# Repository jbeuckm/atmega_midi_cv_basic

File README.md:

# atmega_midi_cv_basic
Simple gate+pitch+velocity with one 4822

Portamento time is controlled by MIDI CC #5.

When more than one MIDI note is active, the frequency CV is set according to the value of MIDI CC #80 as follows:

CC #80 | Note Priority
--- | ---   
0-31 | Lowest Note
32-63 | Highest Note
64-127 | Highest Velocity (default)

The MIDI channel can be set by sending the following SYSEX message: 
`0x77 0x16 0x01 0x00 0xcc` where cc is the new channel.

Parts placement for Release v0.5:

For 6N137 instead of 6N138, build with these changes:

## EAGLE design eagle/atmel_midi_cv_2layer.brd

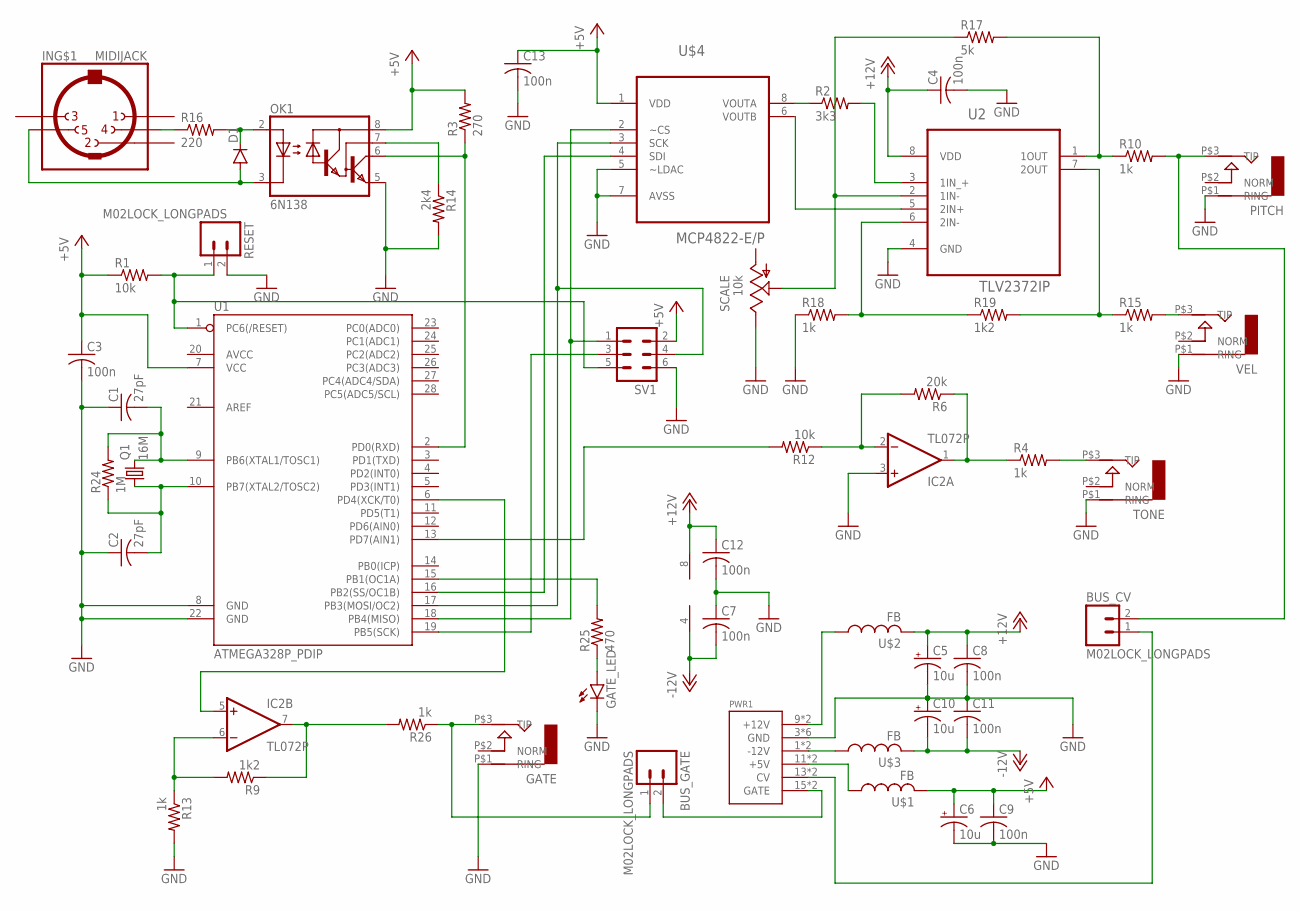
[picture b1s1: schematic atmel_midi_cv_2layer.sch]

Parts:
BUS_CV: M02LOCK_LONGPADS; 1X02_LOCK_LONGPADS
BUS_GATE: M02LOCK_LONGPADS; 1X02_LOCK_LONGPADS
C1, C2: 27pF; C025-040X050
C3, C4, C7, C8, C9, C11, C12, C13: 100n; C050-024X044
C5, C6, C10: 10u; B45181A
D1: DIODE1N4148; DIODE-1N4148
GATE: AUDIO-JACKITEAD; JACK-90DEG-ITEAD
GATE_LED: LED3MM
IC2: TL072P; DIL08
IN: MIDIJACK; CP-2350
OK1: 6N138; DIL08
PITCH: AUDIO-JACKITEAD; JACK-90DEG-ITEAD
PWR1: POWER; POWER_16
Q1: 16M; HC49/S
R1, R12: 10k; 0207/7
R2: 3k3; 0207/7
R3: 270; 0207/7
R4, R10, R13, R15, R18, R26: 1k; 0207/7
R6: 20k; 0207/7
R9, R19: 1k2; 0207/7
R14: 2k4; 0207/7
R16: 220; 0207/7
R17: 5k; 0207/7
R24: 1M; 0207/7
R25: 470; 0207/7
RESET: M02LOCK_LONGPADS; 1X02_LOCK_LONGPADS
SCALE: 10k; B64W
SV1: MA03-2
TONE: AUDIO-JACKITEAD; JACK-90DEG-ITEAD
U1: ATMEGA328P_PDIP; DIL28-3
U2: TLV2372IP; DIP254P762X508-8
U$1, U$2, U$3: FB
U$4: MCP4822-E/P; DIP254P762X432-8
VEL: AUDIO-JACKITEAD; JACK-90DEG-ITEAD

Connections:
+5V: C3.1, C6.+, C9.1, C13.1, OK1.8 (VCC), R1.1, R3.2, SV1.2, U1.7 (VCC), U$1.P$2 (2), U$4.1 (VDD)
+12V: C4.1, C5.+, C8.1, C12.1, IC2.8 (V+), U2.8 (VDD), U$2.P$2 (2)
-12V: C7.2, C10.-, C11.2, IC2.4 (V-), U$3.P$2 (2)
GND: C1.1, C2.1, C3.2, C4.2, C5.-, C6.-, C7.1, C8.2, C9.2, C10.+, C11.1, C12.2, C13.2, GATE.P$1 (RING), GATE_LED.K (C), IC2.3 (+IN), OK1.5 (GND), PITCH.P$1 (RING), PWR1.3 (GND), PWR1.4 (GND), PWR1.5 (GND), PWR1.6 (GND), PWR1.7 (GND), PWR1.8 (GND), R13.2, R14.2, R18.1, RESET.2, SCALE.E, SV1.6, TONE.P$1 (RING), U1.8 (GND), U1.22 (GND), U2.4 (GND), U$4.5 (~LDAC), U$4.7 (AVSS), VEL.P$1 (RING)
unnamed: BUS_GATE.2, PWR1.15 (GATE), PWR1.16 (GATE)
unnamed: SV1.3, U1.19 (PB5(SCK))
unnamed: C1.2, Q1.2, R24.2, U1.9 (PB6(XTAL1/TOSC1))
unnamed: C2.2, Q1.1, R24.1, U1.10 (PB7(XTAL2/TOSC2))
unnamed: D1.C, OK1.2 (A), R16.2
unnamed: IN.4, R16.1
unnamed: BUS_CV.2, PITCH.P$3 (TIP), R10.2
unnamed: IC2.6 (-IN), R9.2, R13.1
unnamed: PWR1.9 (+12V), PWR1.10 (+12V), U$2.P$1 (1)
unnamed: BUS_CV.1, PWR1.13 (CV), PWR1.14 (CV)
unnamed: IC2.7 (OUT), R9.1, R26.2
unnamed: PWR1.1 (-12V), PWR1.2 (-12V), U$3.P$1 (1)
unnamed: GATE_LED.A, R25.1
unnamed: R15.2, VEL.P$3 (TIP)
unnamed: R25.2, U1.15 (PB1(OC1A))
unnamed: R12.2, U1.13 (PD7(AIN1))
unnamed: IC2.5 (+IN), U1.6 (PD4(XCK/T0))
unnamed: R2.1, U$4.8 (VOUTA)
unnamed: R4.2, TONE.P$3 (TIP)
unnamed: SV1.4, U1.17 (PB3(MOSI/OC2)), U$4.3 (SCK)
unnamed: U1.16 (PB2(SS/OC1B)), U$4.4 (SDI)
unnamed: IC2.2 (-IN), R6.2, R12.1
unnamed: OK1.6 (VO), R3.1, U1.2 (PD0(RXD))
unnamed: BUS_GATE.1, GATE.P$3 (TIP), R26.1
unnamed: OK1.7 (VB), R14.1
unnamed: D1.A, IN.5, OK1.3 (C)
unnamed: PWR1.11 (+5V), PWR1.12 (+5V), U$1.P$1 (1)
unnamed: IC2.1 (OUT), R4.1, R6.1
unnamed: R2.2, U2.3 (1IN_+)
unnamed: R17.1, SCALE.P$1 (S), SCALE.S, U2.2 (1IN-)
unnamed: R18.2, R19.1, U2.6 (2IN-)
unnamed: R15.1, R19.2, U2.7 (2OUT)
unnamed: U2.5 (2IN+), U$4.6 (VOUTB)
unnamed: R10.1, R17.2, U2.1 (1OUT)
unnamed: R1.2, RESET.1, SV1.5, U1.1 (PC6(/RESET))
unnamed: SV1.1, U1.18 (PB4(MISO)), U$4.2 (~CS)

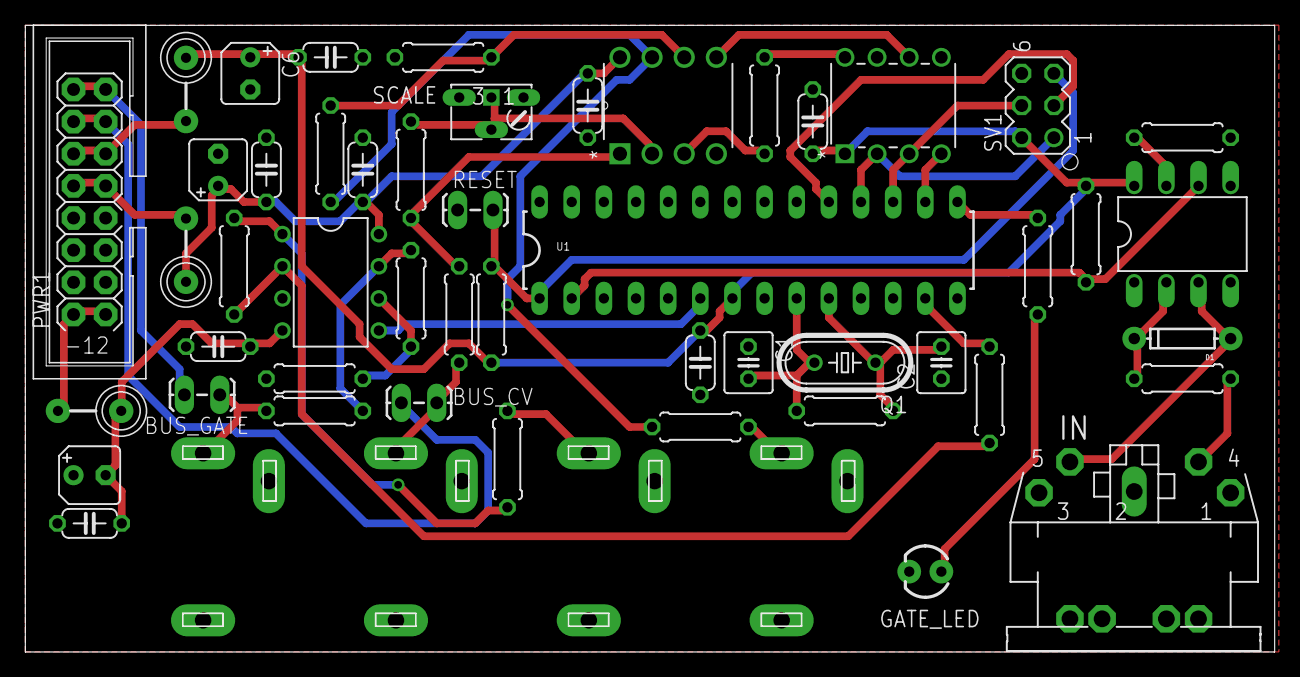
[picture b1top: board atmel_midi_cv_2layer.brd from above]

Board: 2 copper layers, 98.6 x 49.4 mm, 53 parts (0 on the bottom side), 40 nets.

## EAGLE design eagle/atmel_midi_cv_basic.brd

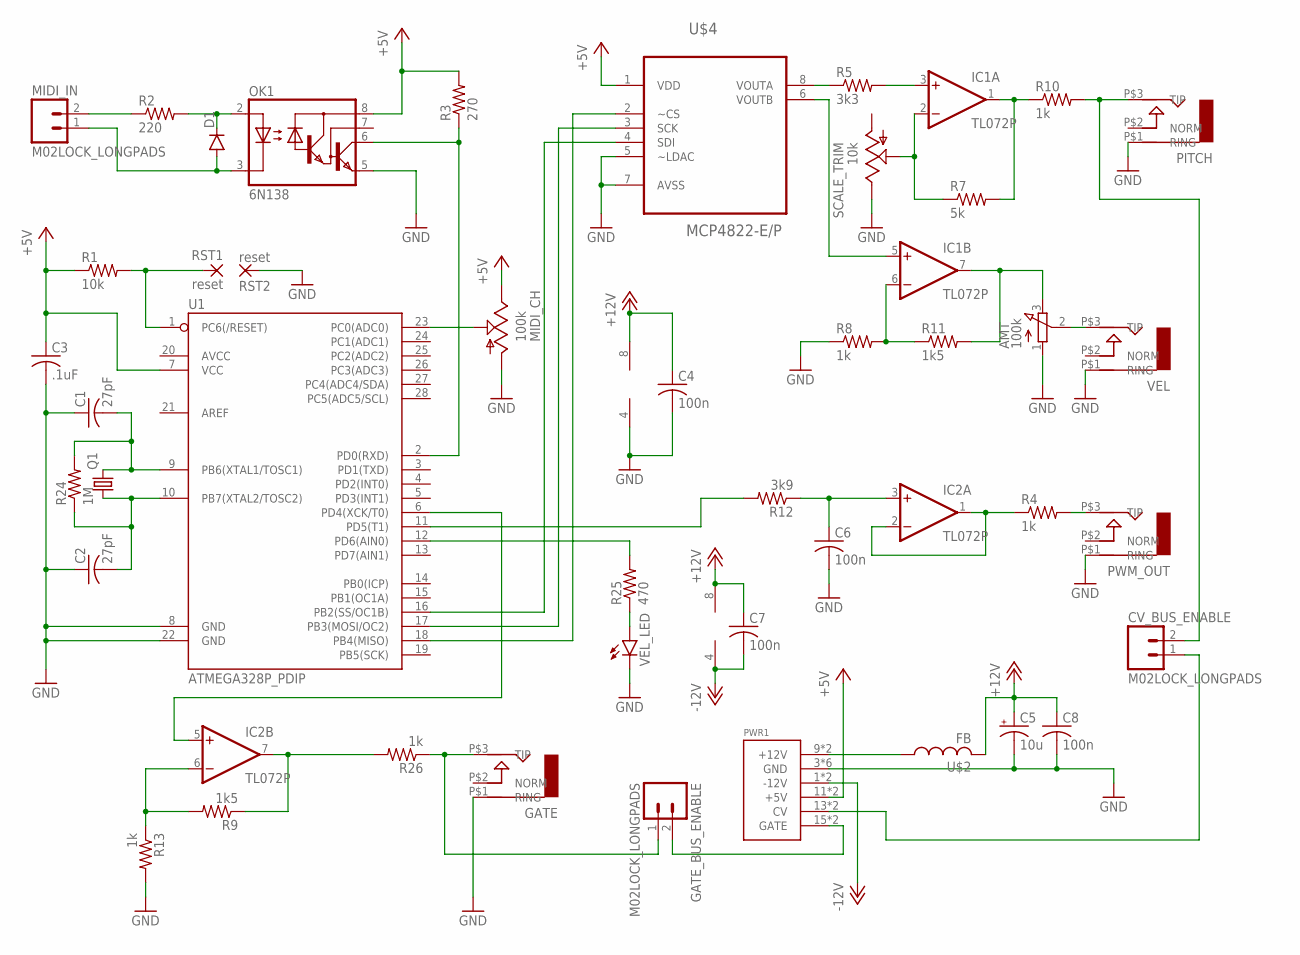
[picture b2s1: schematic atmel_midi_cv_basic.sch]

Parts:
AMT: 100k; 3RP/1610N
C1, C2: 27pF; C025-040X050
C3: .1uF; C050-024X044
C4, C6, C7, C8: 100n; C050-024X044
C5: 10u; B45181A
CV_BUS_ENABLE: M02LOCK_LONGPADS; 1X02_LOCK_LONGPADS
D1: DIODE1N4148; DIODE-1N4148
GATE: AUDIO-JACK; ERTHENVAR-JACK-90DEG
GATE_BUS_ENABLE: M02LOCK_LONGPADS; 1X02_LOCK_LONGPADS
IC1, IC2: TL072P; DIL08
MIDI_CH: 100k; B64W
MIDI_IN: M02LOCK_LONGPADS; 1X02_LOCK_LONGPADS
OK1: 6N138; DIL08
PITCH: AUDIO-JACK; ERTHENVAR-JACK-90DEG
PWM_OUT: AUDIO-JACK; ERTHENVAR-JACK-90DEG
PWR1: POWER; POWER_16
Q1: CRYSTALHC49S; HC49/S
R1: 10k; 0207/7
R2: 220; 0207/7
R3: 270; 0207/7
R4, R8, R10, R13, R26: 1k; 0207/7
R5: 3k3; 0207/7
R7: 5k; 0207/7
R9, R11: 1k5; 0207/7
R12: 3k9; 0207/7
R24: 1M; 0207/7
R25: 470; 0207/7
RST1, RST2: reset; 2,54/0,9
SCALE_TRIM: 10k; B64W
U1: ATMEGA328P_PDIP; DIL28-3
U$2: FB
U$4: MCP4822-E/P; DIP254P762X432-8
VEL: AUDIO-JACK; ERTHENVAR-JACK-90DEG
VEL_LED: LED5MM

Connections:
+5V: C3.1, MIDI_CH.E, OK1.8 (VCC), PWR1.11 (+5V), PWR1.12 (+5V), R1.1, R3.2, U1.7 (VCC), U$4.1 (VDD)
+12V: C4.1, C5.+, C7.1, C8.1, IC1.8 (V+), IC2.8 (V+), U$2.P$2 (2)
-12V: C7.2, IC2.4 (V-), PWR1.1 (-12V), PWR1.2 (-12V)
GND: VEL_LED.K (C)
unnamed: GATE_BUS_ENABLE.2, PWR1.15 (GATE), PWR1.16 (GATE)
unnamed: R5.1, U$4.8 (VOUTA)
unnamed: D1.A, MIDI_IN.1, OK1.3 (C)
unnamed: C1.2, Q1.2, R24.2, U1.9 (PB6(XTAL1/TOSC1))
unnamed: C2.2, Q1.1, R24.1, U1.10 (PB7(XTAL2/TOSC2))
unnamed: IC1.3 (+IN), R5.2
unnamed: D1.C, OK1.2 (A), R2.2
unnamed: MIDI_IN.2, R2.1
unnamed 12: CV_BUS_ENABLE.2, PITCH.P$3 (TIP), R10.2; also elsewhere on the board
unnamed: IC2.6 (-IN), R9.2, R13.1
unnamed: PWR1.9 (+12V), PWR1.10 (+12V), U$2.P$1 (1)
unnamed: IC1.2 (-IN), R7.1, SCALE_TRIM.S
unnamed: IC1.6 (-IN), R8.2, R11.1
unnamed: IC1.5 (+IN), U$4.6 (VOUTB)
unnamed: CV_BUS_ENABLE.1, PWR1.13 (CV), PWR1.14 (CV)
unnamed: IC2.7 (OUT), R9.1, R26.2
unnamed: AMT.3 (E), IC1.7 (OUT), R11.2
unnamed: R25.1, VEL_LED.A
unnamed: MIDI_CH.S, U1.23 (PC0(ADC0))
unnamed: R25.2, U1.12 (PD6(AIN0))
unnamed: R12.2, U1.11 (PD5(T1)), U1.19 (PB5(SCK))
unnamed: IC2.5 (+IN), U1.6 (PD4(XCK/T0))
unnamed: IC2.1 (OUT), IC2.2 (-IN), R4.1
unnamed 27: PWM_OUT.P$3 (TIP), R4.2; also elsewhere on the board
unnamed: U1.17 (PB3(MOSI/OC2)), U$4.3 (SCK)
unnamed: U1.16 (PB2(SS/OC1B)), U$4.4 (SDI)
unnamed: IC1.1 (OUT), R7.2, R10.1
unnamed: C6.1, IC2.3 (+IN), R12.1
unnamed 32: AMT.1 (A), C1.1, C2.1, C3.2, C4.2, C5.-, C6.2, C8.2, GATE.P$1 (RING), IC1.4 (V-), MIDI_CH.A, OK1.5 (GND), PITCH.P$1 (RING), PWM_OUT.P$1 (RING), PWR1.3 (GND), PWR1.4 (GND), PWR1.5 (GND), PWR1.6 (GND), PWR1.7 (GND), PWR1.8 (GND), R8.1, R13.2, RST2.1, SCALE_TRIM.E, U1.8 (GND), U1.22 (GND), U$4.5 (~LDAC), U$4.7 (AVSS), VEL.P$1 (RING); also elsewhere on the board
unnamed: OK1.6 (VO), R3.1, U1.2 (PD0(RXD))
unnamed: GATE.P$3 (TIP), GATE_BUS_ENABLE.1, R26.1
unnamed: R1.2, RST1.1, U1.1 (PC6(/RESET))
unnamed: U1.18 (PB4(MISO)), U$4.2 (~CS)
unnamed: AMT.2 (S), VEL.P$3 (TIP)

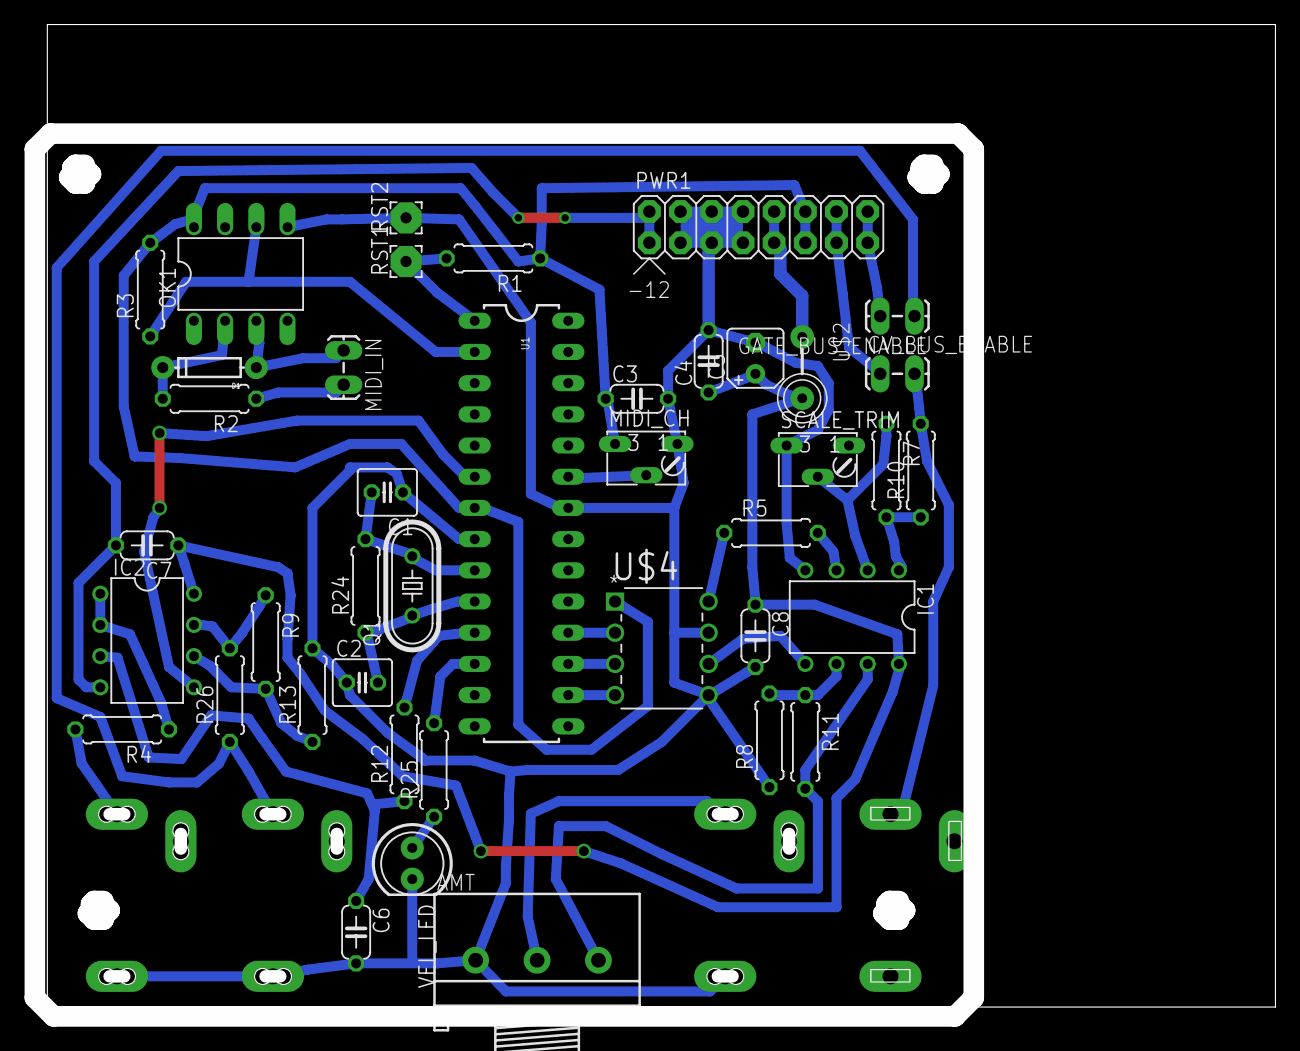
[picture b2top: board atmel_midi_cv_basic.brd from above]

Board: 2 copper layers, 100.2 x 79.9 mm, 45 parts (0 on the bottom side), 37 nets.

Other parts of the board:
JCK1: AUDIO-JACKITEAD; JACK-90DEG-ITEAD
TONE_OUT: AUDIO-JACK; ERTHENVAR-JACK-90DEG

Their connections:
unnamed 12: JCK1.P$3; also elsewhere on the board
unnamed 27: TONE_OUT.P$3; also elsewhere on the board
unnamed 32: JCK1.P$1, TONE_OUT.P$1; also elsewhere on the board

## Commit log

2016-01-05 velocity gate led
2016-01-05 board near complete
2016-01-06 sloppy routed
2016-01-06 almost
2016-01-06 will try cut
2016-01-06 led fixed
2016-01-08 playing scale to indicate midi channel by number of notes
2016-01-08 no neg supply
2016-01-10 swapping atmega pin 16 and 17 for layout convenience
2016-01-12 possible route
2016-01-12 routed
2016-01-12 new gcode
2016-01-12 layout tweaked
2016-01-14 fixed led output to pwm pin and schematic consistent
2016-01-30 panel
2016-08-14 implemented all notes off controller and noteoff for count below zero
2016-08-20 cleaned up some routes
2016-08-23 corrected wrong gate pin and tl072 back to bipolar to prevent locking
2017-08-25 rail2rail pitch amp, tone output, improved decoupling, board mount midi jack, more isolation
2017-08-25 copied over gitignore
2017-08-25 merged many 9 to GND
2017-08-26 started software update
2017-08-26 removed old files
2017-08-26 added url and release to silkscreen
2017-08-26 removed part number clutter
2017-08-26 new png
2017-08-26 trying to ignore lock files
2017-08-26 layout tweaks
2017-08-27 sent the files
2017-09-10 front panel started for new version
2017-09-20 ICSP added and rerouted
2017-09-20 updated power with shroud
2017-09-23 screenshot for first version layout
2017-09-23 implementing notebook for priority note out
2017-09-23 set note priority with midi cc 80
2017-09-23 setting pitch on 1khz interrupt and just sending target freq code
2017-09-23 removed pitch dac set from setup calibration value
2017-10-14 turned off 1khz timer and implemented pitchbend for tone output
2017-10-15 gate pin added and working same as LED pin
2017-10-18 preparing to update dac and tone frequency at audio rate to avoid timer interrupt conflicts
2017-10-19 modified dac library to use fast writes
2017-10-20 portamento but depends on frequency
2017-10-20 processing portamento with millis() in the loop()
2017-10-21 fixed type and tuned portamento time
2017-11-04 updated panel
2017-11-06 adjusted midi label location
2017-11-11 minor tweaks
2017-12-08 route better clearance for midi resistor and scale pot
2017-12-08 label tweaks and power filter moved
2017-12-10 6n137 and MIDI documentation
2017-12-10 corrected doc

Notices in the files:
parts and their libraries:
SparkFun-Connectors: Licensing: Creative Commons ShareAlike 4.0 International - https://creativecommons.org/licenses/by-sa/4.0
